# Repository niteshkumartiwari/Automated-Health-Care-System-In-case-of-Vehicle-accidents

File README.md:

# Automated-Health-Care-System-In-case-of-Vehicle-accidents
video Link [https://drive.google.com/open?id=0B15X60Iu4NJ0ZVRlSzBhU2pFM3M]

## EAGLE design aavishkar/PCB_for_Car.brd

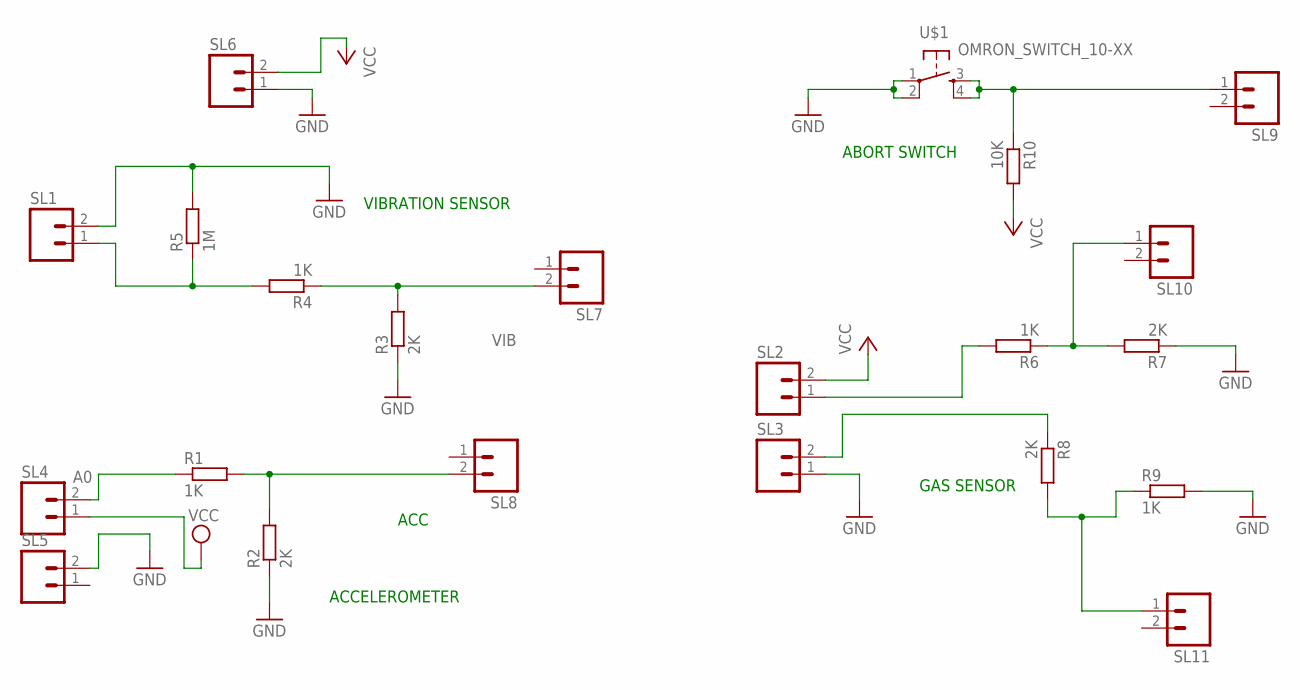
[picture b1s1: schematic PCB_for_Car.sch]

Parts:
R1, R4, R6, R9: 1K; 0204/7
R2, R3, R7, R8: 2K; 0204/7
R5: 1M; 0204/7
R10: 10K; 0204/7
SL1, SL2, SL3, SL4, SL5, SL6, SL7, SL8, SL9, SL10, SL11: M02; 02P
U$1: OMRON_SWITCH_10-XX; B3F-10XX

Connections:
A0: R1.1, SL4.2
GND: R2.1, R3.1, R5.2, R7.1, R9.2, SL1.2, SL3.1, SL5.2, SL6.1, U$1.1, U$1.2 (P1)
unnamed: R1.2, R2.2, SL8.2
unnamed: R6.2, SL2.1
unnamed: R4.2, R5.1, SL1.1
unnamed: R3.2, R4.1, SL7.2
unnamed: R6.1, R7.2, SL10.1
unnamed: R8.1, SL3.2
unnamed: R8.2, R9.1, SL11.1
unnamed: R10.1, SL9.1, U$1.3 (S), U$1.4 (S1)
VCC: R10.2, SL2.2, SL4.1, SL6.2

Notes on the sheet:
ACCELEROMETER
VIBRATION SENSOR
ABORT SWITCH
GAS SENSOR
VIB
ACC

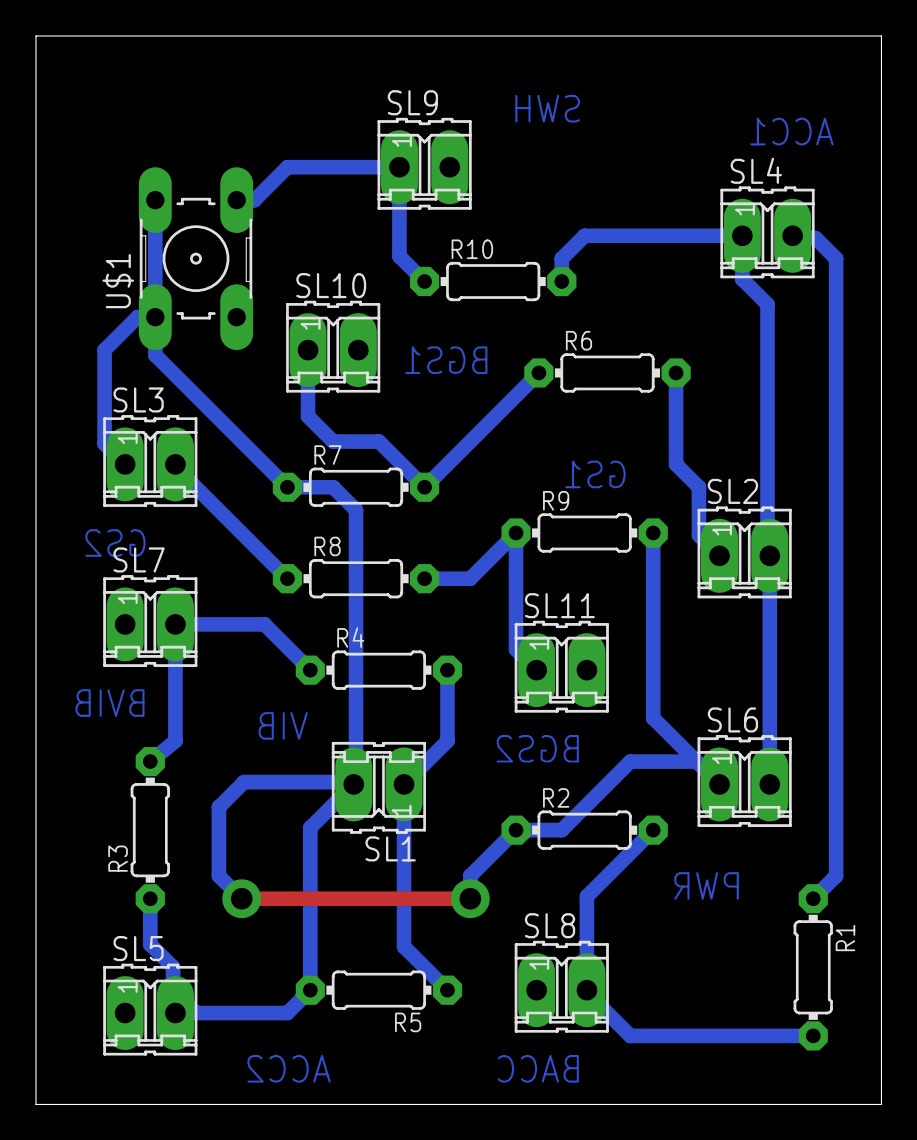
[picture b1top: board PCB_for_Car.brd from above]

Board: 2 copper layers, 47.0 x 59.4 mm, 22 parts (0 on the bottom side), 11 nets.

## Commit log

2017-04-23 files added
2020-01-30 video link added
2020-01-30 Bump werkzeug from 0.11.11 to 0.15.3 in /aavishkar
    Bumps [werkzeug](https://github.com/pallets/werkzeug) from 0.11.11 to 0.15.3.
    - [Release notes](https://github.com/pallets/werkzeug/releases)
    - [Changelog](https://github.com/pallets/werkzeug/blob/master/CHANGES.rst)
    - [Commits](https://github.com/pallets/werkzeug/compare/0.11.11...0.15.3)
2020-01-30 Bump flask from 0.11.1 to 1.0 in /aavishkar
    Bumps [flask](https://github.com/pallets/flask) from 0.11.1 to 1.0.
    - [Release notes](https://github.com/pallets/flask/releases)
    - [Changelog](https://github.com/pallets/flask/blob/master/CHANGES.rst)
    - [Commits](https://github.com/pallets/flask/compare/0.11.1...1.0)
2021-03-19 Bump jinja2 from 2.8 to 2.11.3 in /aavishkar
    Bumps [jinja2](https://github.com/pallets/jinja) from 2.8 to 2.11.3.
    - [Release notes](https://github.com/pallets/jinja/releases)
    - [Changelog](https://github.com/pallets/jinja/blob/master/CHANGES.rst)
    - [Commits](https://github.com/pallets/jinja/compare/2.8...2.11.3)
2023-02-02 Bump werkzeug from 0.11.11 to 0.15.5 in /aavishkar
    Bumps [werkzeug](https://github.com/pallets/werkzeug) from 0.11.11 to 0.15.5.
    - [Release notes](https://github.com/pallets/werkzeug/releases)
    - [Changelog](https://github.com/pallets/werkzeug/blob/main/CHANGES.rst)
    - [Commits](https://github.com/pallets/werkzeug/compare/0.11.11...0.15.5)
    ---
    updated-dependencies:
